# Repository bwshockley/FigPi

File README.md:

# FigPi
Minifigure sized RP2040 based development board.

This has not been tested.  I have ordered prototype boards, so if you use this repo, please be prepared to have things not work.

## Board Definition for CircuitPython
[Fig Pi Board Definition - Local](https://github.com/bwshockley/circuitpython/tree/bwshockley-figpi/ports/raspberrypi/boards/bwshockley_figpi)

TODO: Once this board definition is pulled into the Adafruit repo, change link to the Adafruit repo.

## Changelog
**v1.1**
* Attached USB_BOOT to GPIO20, Pin 31
* Moved C12 to make room for new signal.

**v1.5**
* Changed all JST connectors to 4-pin.
* Moved SWDIO and SWCLK to test pads.
* Added APA102-2020 LEDs to make a 3 x 3 matrix.

**v1.6**
* Minor cosmetic changes to accomidate 'Status' label.

**v1.7**
* Fixed potential manufacturing limitation with ground vias.

**v2.1**
* Significant layout change to fix errors, move to mostly 0402 size passives, DFM, and more.

**v2.2**
* Updated the stemma connectors (i2c).  Pins were swapped - fixed the order.

**v2.3**
* Minor updates to routing, cleanup of vias, additional DRC checks.  Added silkscreen details.

**v2.3.1**
* Modified the silkscreen label from QWIIC0 and QWIIC1 to I2C0 and I2C1

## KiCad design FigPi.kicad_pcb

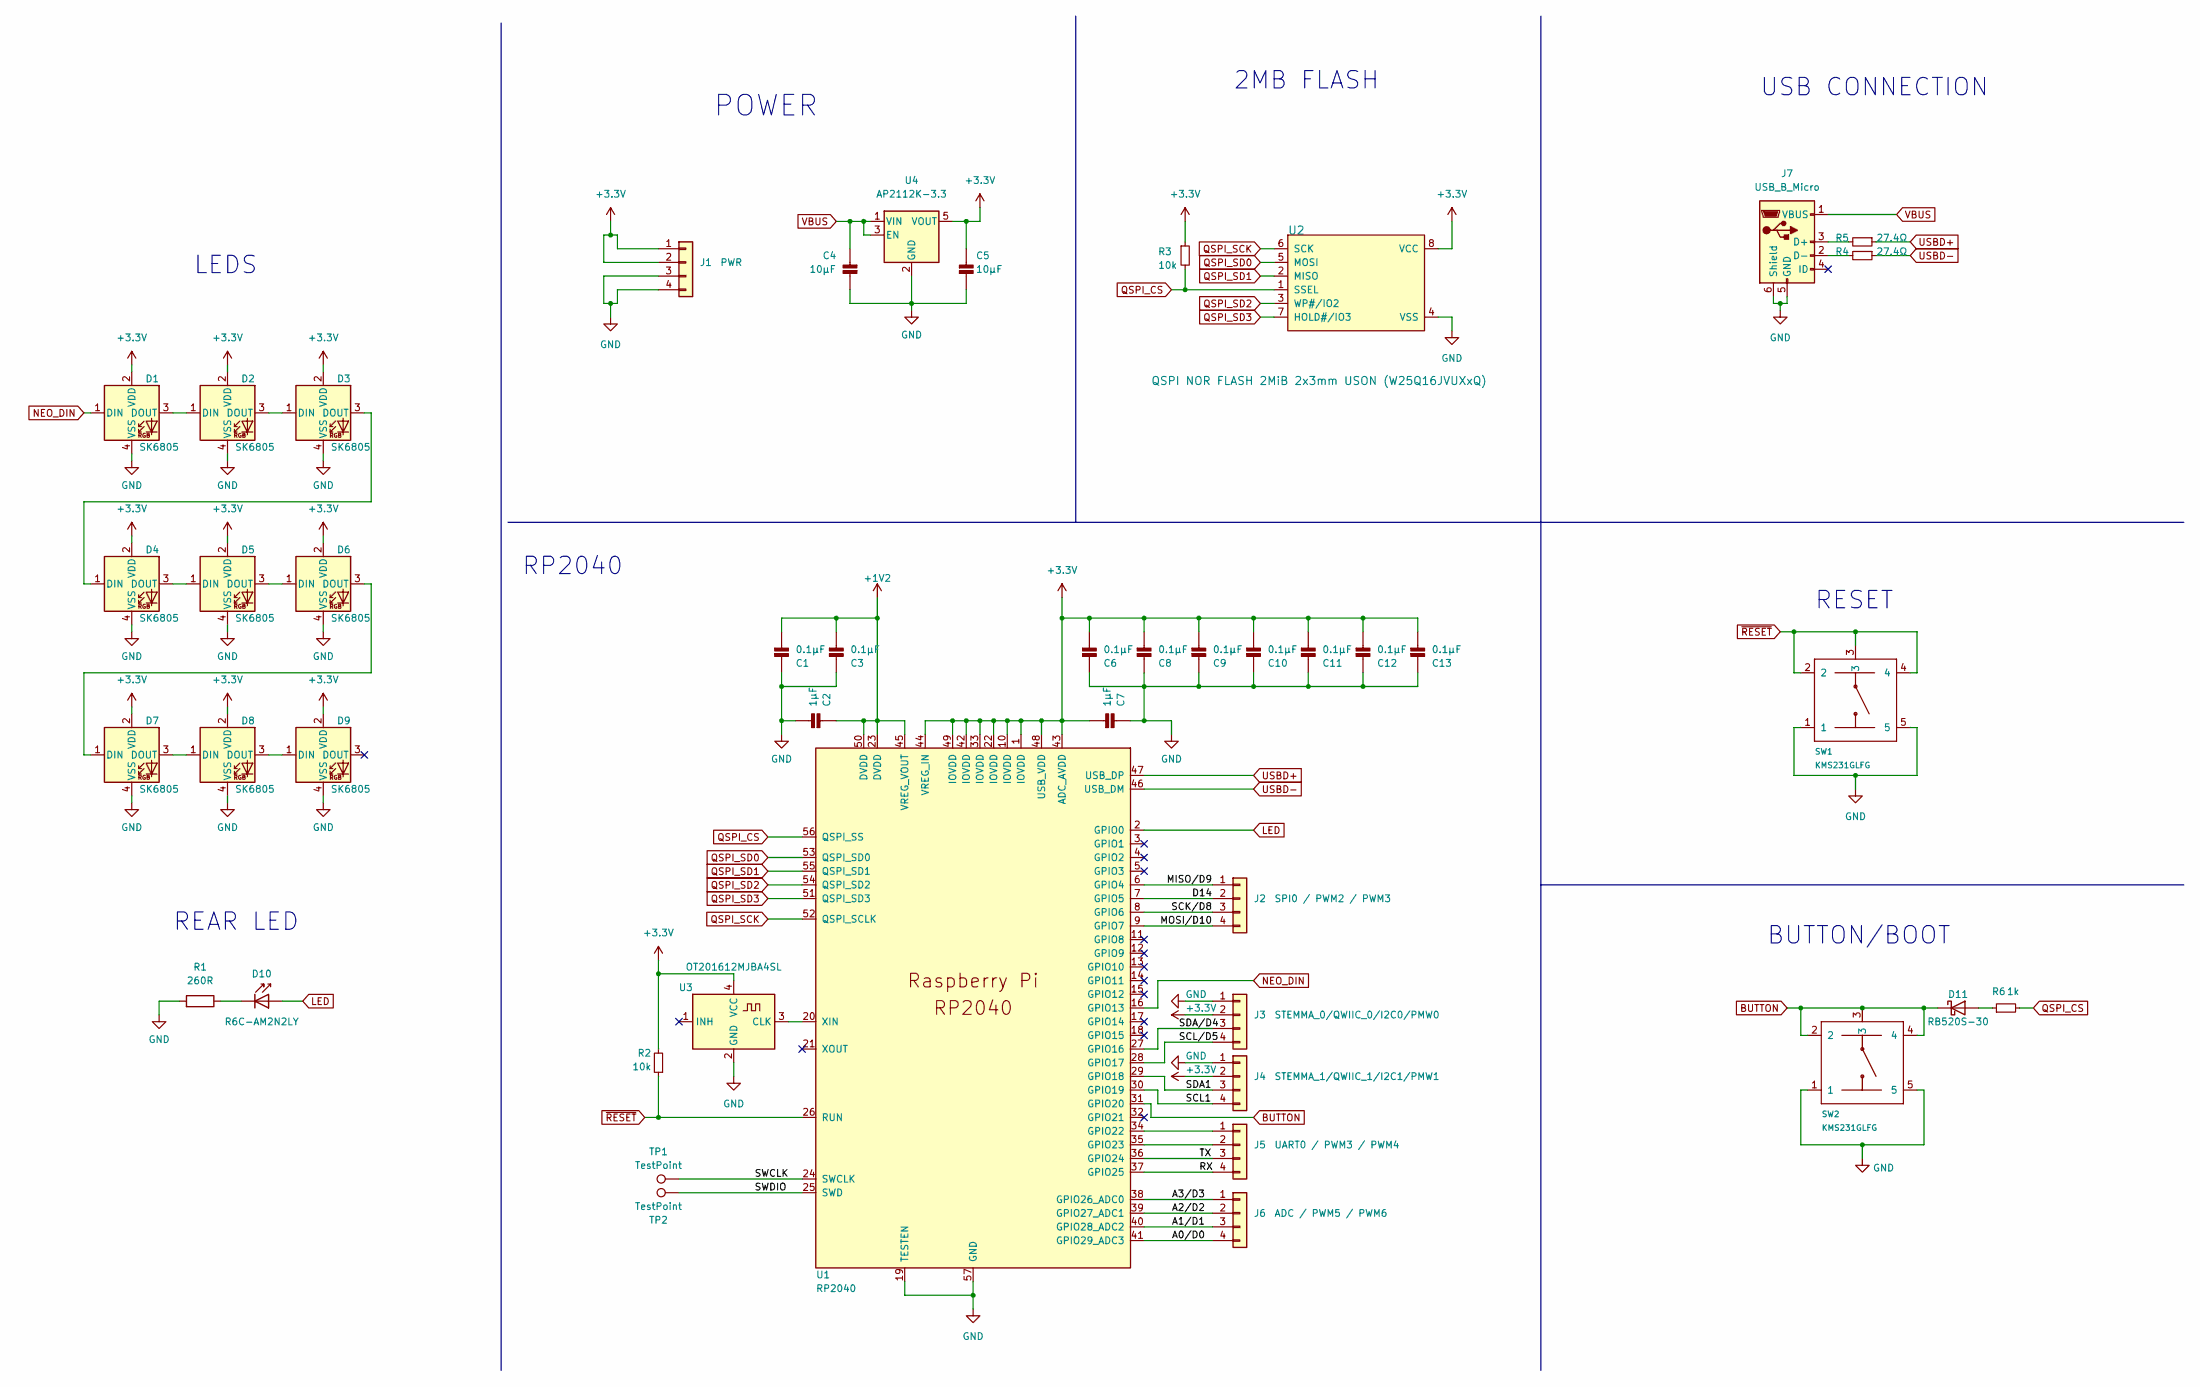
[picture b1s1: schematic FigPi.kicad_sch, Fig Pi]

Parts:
C1, C3, C6, C8, C9, C10, C11, C12, C13: 0.1µF; C_0402_1005Metric; JLCPCB C105882
C2, C7: 1µF; C_0402_1005Metric; JLCPCB C52923
C4, C5: 10µF; R_0603_1608Metric; JLCPCB C85713
D1, D2, D3, D4, D5, D6, D7, D8, D9: SK6805; LED_SK6805_EC15_1.5x1.5mm; JLCPCB C2890035
D10: R6C-AM2N2LY; LED_1.1x1.7mm; JLCPCB C605457
D11: RB520S-30; D_SOD-523; JLCPCB C8522
J1: PWR; JST_SH_SM04B-SRSS-TB_1x04-1MP_P1.00mm_Horizontal; JLCPCB C160404
J2: SPI0 / PWM2 / PWM3; JST_SH_SM04B-SRSS-TB_1x04-1MP_P1.00mm_Horizontal; JLCPCB C160404
J3: STEMMA_0/QWIIC_0/I2C0/PMW0; JST_SH_SM04B-SRSS-TB_1x04-1MP_P1.00mm_Horizontal; JLCPCB C160404
J4: STEMMA_1/QWIIC_1/I2C1/PMW1; JST_SH_SM04B-SRSS-TB_1x04-1MP_P1.00mm_Horizontal; JLCPCB C160404
J5: UART0 / PWM3 / PWM4; JST_SH_SM04B-SRSS-TB_1x04-1MP_P1.00mm_Horizontal; JLCPCB C160404
J6: ADC / PWM5 / PWM6; JST_SH_SM04B-SRSS-TB_1x04-1MP_P1.00mm_Horizontal; JLCPCB C160404
J7: USB_B_Micro; USB_Micro-B_Molex_47346-0001
R1: 260R; R_0603_1608Metric; JLCPCB C227740
R2, R3: 10k; R_0402_1005Metric; JLCPCB C144731
R4, R5: 27.4Ω; R_0402_1005Metric; JLCPCB C274349
R6: 1k; R_0402_1005Metric; JLCPCB C105637
SW1, SW2: KMS231GLFG; KMS_SWITCH; JLCPCB C221701
TP1, TP2: TestPoint; TestPoint_Pad_D1.0mm
U1: RP2040; QFN-56-1EP_7x7mm_P0.4mm_EP3.2x3.2mm; JLCPCB C2040
U2: QSPI NOR FLASH 2MiB 2x3mm USON (W25Q16JVUXxQ); USON-8_L3.0-W2.0-P0.50-BL-EP; JLCPCB C2843335
U3: OT201612MJBA4SL; Oscillator_SMD_Yangzing_Tech_SMD2016-4P; JLCPCB P/N C669076
U4: AP2112K-3.3; SOT-23-5; JLCPCB C3021085

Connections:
+1V2: C1.2, C2.1, C3.2, U1.23 (DVDD), U1.45 (VREG_VOUT), U1.50 (DVDD)
+3.3V: C5.1, C6.2, C7.2, C8.2, C9.2, C10.2, C11.2, C12.2, C13.2, D1.2 (VDD), D2.2 (VDD), D3.2 (VDD), D4.2 (VDD), D5.2 (VDD), D6.2 (VDD), D7.2 (VDD), D8.2 (VDD), D9.2 (VDD), J1.1, J1.2, J3.2, J4.2, R2.2, R3.1, U1.1 (IOVDD), U1.10 (IOVDD), U1.22 (IOVDD), U1.33 (IOVDD), U1.42 (IOVDD), U1.43 (ADC_AVDD), U1.44 (VREG_IN), U1.48 (USB_VDD), U1.49 (IOVDD), U2.8 (VCC), U3.4 (VCC), U4.5 (VOUT)
/A0/D0: J6.4, U1.41 (GPIO29_ADC3)
/A1/D1: J6.3, U1.40 (GPIO28_ADC2)
/A2/D2: J6.2, U1.39 (GPIO27_ADC1)
/A3/D3: J6.1, U1.38 (GPIO26_ADC0)
/D14: J2.2, U1.7 (GPIO5)
/MISO/D9: J2.1, U1.6 (GPIO4)
/MOSI/D10: J2.4, U1.9 (GPIO7)
/RX: J5.4, U1.37 (GPIO25)
/SCK/D8: J2.3, U1.8 (GPIO6)
/SCL1: J4.4, U1.30 (GPIO19)
/SCL/D5: J3.4, U1.28 (GPIO17)
/SDA1: J4.3, U1.29 (GPIO18)
/SDA/D4: J3.3, U1.27 (GPIO16)
/SWCLK: TP1.1, U1.24 (SWCLK)
/SWDIO: TP2.1, U1.25 (SWD)
/TX: J5.3, U1.36 (GPIO24)
BUTTON: D11.1 (K), SW2.2, SW2.3, SW2.4, U1.31 (GPIO20)
GND: C1.1, C2.2, C3.1, C4.1, C5.2, C6.1, C7.1, C8.1, C9.1, C10.1, C11.1, C12.1, C13.1, D1.4 (VSS), D2.4 (VSS), D3.4 (VSS), D4.4 (VSS), D5.4 (VSS), D6.4 (VSS), D7.4 (VSS), D8.4 (VSS), D9.4 (VSS), J1.3, J1.4, J3.1, J4.1, J7.5 (GND), J7.6 (Shield), R1.2, SW1.1, SW1.5, SW2.1, SW2.5, U1.19 (TESTEN), U1.57 (GND), U2.4 (VSS), U3.2 (GND), U4.2 (GND)
LED: D10.2 (A), U1.2 (GPIO0)
NEO_DIN: D1.1 (DIN), U1.16 (GPIO13)
unnamed: D1.3 (DOUT), D2.1 (DIN)
unnamed: D2.3 (DOUT), D3.1 (DIN)
unnamed: D3.3 (DOUT), D4.1 (DIN)
unnamed: D4.3 (DOUT), D5.1 (DIN)
unnamed: D5.3 (DOUT), D6.1 (DIN)
unnamed: D6.3 (DOUT), D7.1 (DIN)
unnamed: D7.3 (DOUT), D8.1 (DIN)
unnamed: D8.3 (DOUT), D9.1 (DIN)
unnamed: D10.1 (C), R1.1
unnamed: D11.2 (A), R6.1
unnamed: J5.1, U1.34 (GPIO22)
unnamed: J5.2, U1.35 (GPIO23)
unnamed: J7.2 (D-), R4.2
unnamed: J7.3 (D+), R5.2
unnamed: U1.20 (XIN), U3.3 (CLK)
QSPI_CS: R3.2, R6.2, U1.56 (QSPI_SS), U2.1 (SSEL)
QSPI_SCK: U1.52 (QSPI_SCLK), U2.6 (SCK)
QSPI_SD0: U1.53 (QSPI_SD0), U2.5 (MOSI)
QSPI_SD1: U1.55 (QSPI_SD1), U2.2 (MISO)
QSPI_SD2: U1.54 (QSPI_SD2), U2.3 (WP#/IO2)
QSPI_SD3: U1.51 (QSPI_SD3), U2.7 (HOLD#/IO3)
USBD+: R5.1, U1.47 (USB_DP)
USBD-: R4.1, U1.46 (USB_DM)
VBUS: C4.2, J7.1 (VBUS), U4.1 (VIN), U4.3 (EN)
~RESET: R2.1, SW1.2, SW1.3, SW1.4, U1.26 (RUN)

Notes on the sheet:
REAR LED
2MB FLASH
RESET
POWER
BUTTON/BOOT
USB CONNECTION
LEDS
RP2040

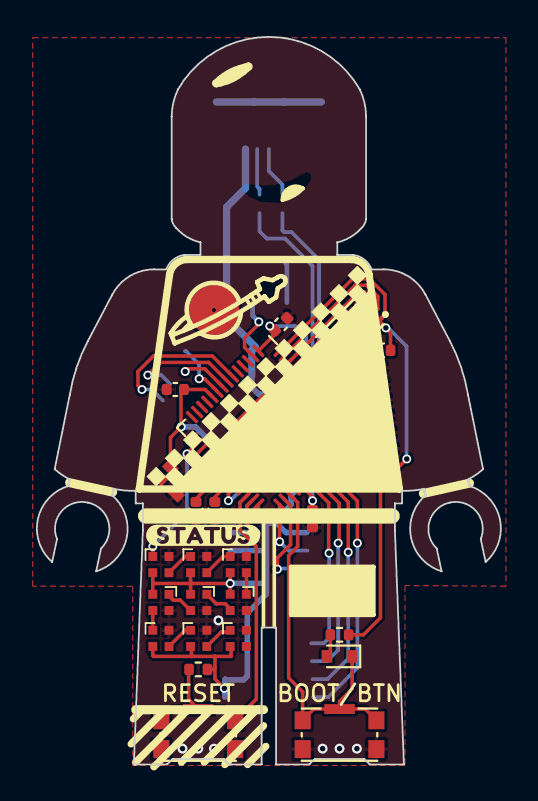
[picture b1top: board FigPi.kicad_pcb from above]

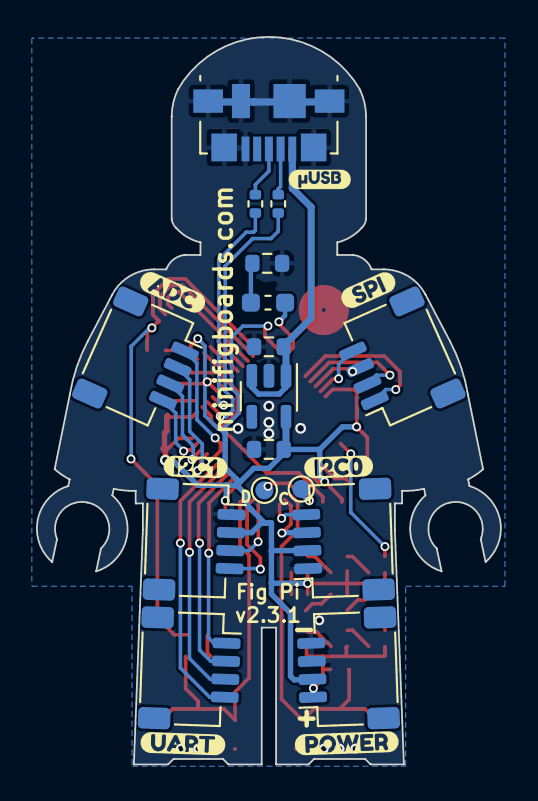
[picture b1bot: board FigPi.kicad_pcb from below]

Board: 2 copper layers, 25.8 x 40.4 mm, 53 parts (23 on the bottom side), 47 nets.

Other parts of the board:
kibuzzard-640B746F: G***; kibuzzard-640B746F
kibuzzard-640F7BF6: G***; kibuzzard-640F7BF6
kibuzzard-640F7C1A: G***; kibuzzard-640F7C1A
kibuzzard-640F7C6F: G***; kibuzzard-640F7C6F
kibuzzard-640F7C7F: G***; kibuzzard-640F7C7F
kibuzzard-640F7D7C: G***; kibuzzard-640F7D7C
kibuzzard-6411F9C1: G***; kibuzzard-6411F9C1
kibuzzard-6411FA03: G***; kibuzzard-6411FA03

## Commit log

2022-07-20 Initial Add - V.10
    Adding the first files. Warning these have not been tested.
2022-07-20 Create README.md
    Created the README
2022-07-20 Connected USBOOT properly to Boot button. Had to move capacitor for new track.
2022-07-20 Update README.md
    Added Change log info for version 1.1
2022-07-21 v1.5 - Changed all JST connections to 4-pin. Added 8 additional APA102 - 2020 LEDs for a 3 x 3 matrix. Rearranged items as needed. Moved SWDIO and SWCLK from JST connector to test pads.
2022-07-21 1.6 - Minor Cosmetic Changes
2022-07-21 Update README.md
    CircuitPython board definition link.
2022-07-21 Update README.md
    Minor format issue fixed.
2022-07-21 v1.7 Fixed potential manufacturing limitation with ground vias.
2023-03-01 Updated to Rev 2.1 - layout changes, smd size changes.
2023-03-10 modified: FigPi.kicad_pcb modified: FigPi.kicad_sch
    Swapped around the stemma connector pins.
2023-03-14 Update to v2.3
    Updated the schematic and board to v2.3.
2023-03-14 Updated git ignore.
    Ignoring production files and other non-design essential files prouced.
2023-03-14 Delete MINI_SAM.pretty directory
    Remove unnecessary directory and file.
2023-03-15 Updated Bottom Silkscreen
    Changed the I2C connector labels.
